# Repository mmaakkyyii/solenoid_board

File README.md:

# solenoid_board
[m5-solenoid_main](https://github.com/mmaakkyyii/m5-solenoid_main)とあわせてソレノイドを駆動するパワーサイドの基板

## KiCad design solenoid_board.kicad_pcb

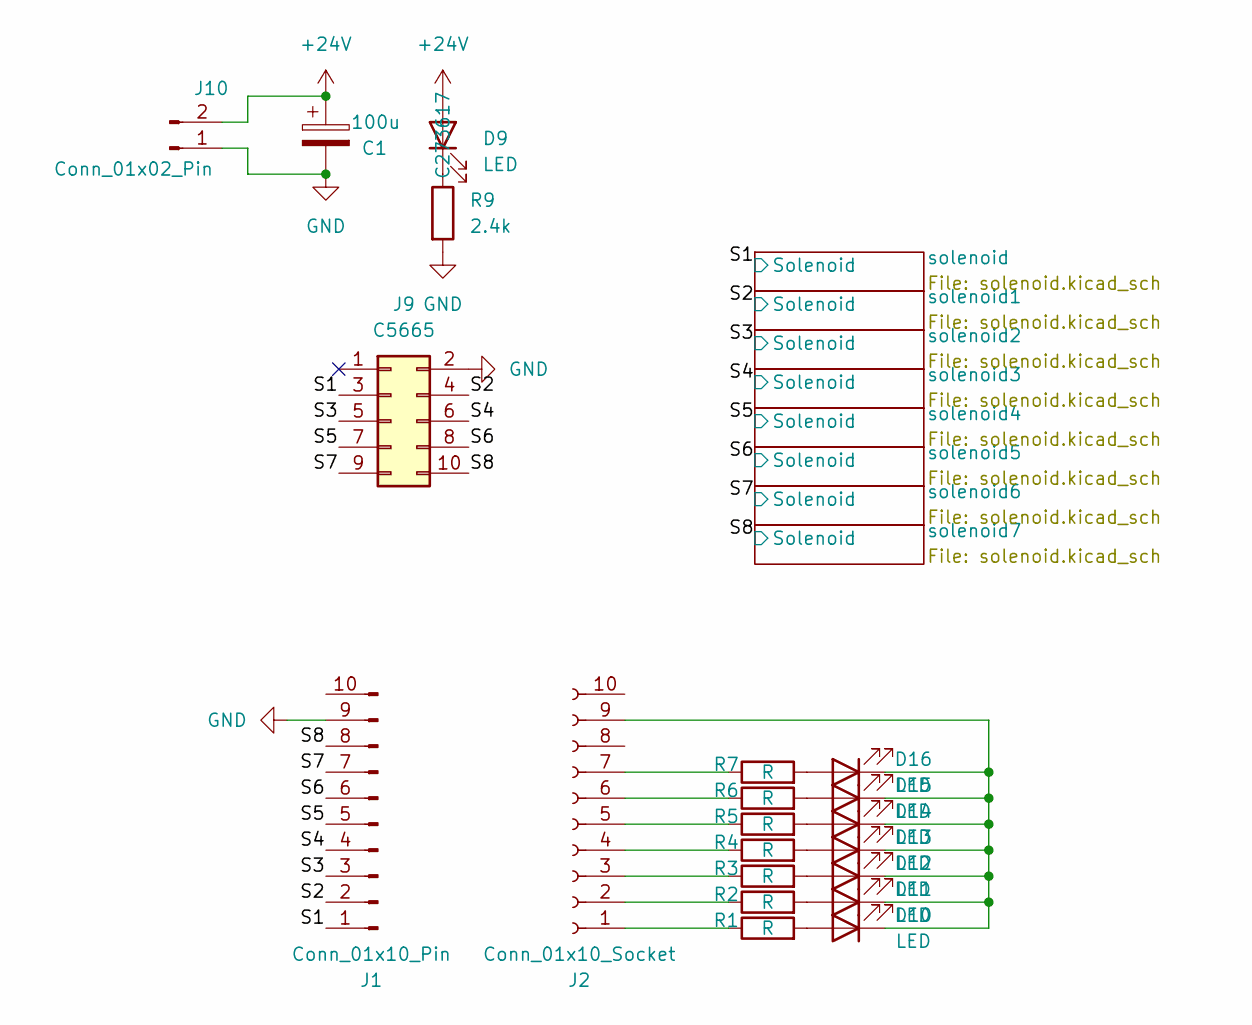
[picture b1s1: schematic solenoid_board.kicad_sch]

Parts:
C1: 100u; CP_Elec_8x10
D9, D10, D11, D12, D13, D14, D15, D16: LED; LED_0603_1608Metric; JLCPCB Parts# C273617
J1: Conn_01x10_Pin; PinSocket_1x10_P2.54mm_Vertical
J2: Conn_01x10_Socket; PinHeader_1x10_P2.54mm_Horizontal
J9: C5665; IDC-Header_2x05_P2.54mm_Vertical
J10: Conn_01x02_Pin; JST_XH_B2B-XH-A_1x02_P2.50mm_Vertical
R1, R2, R3, R4, R5, R6, R7: R; R_0603_1608Metric
R9: 2.4k; R_0603_1608Metric

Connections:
+24V: C1.1, D9.2 (A), J10.2; also elsewhere on the board
/S1: J1.1, J9.3; also elsewhere on the board
/S2: J1.2, J9.4; also elsewhere on the board
/S3: J1.3, J9.5; also elsewhere on the board
/S4: J1.4, J9.6; also elsewhere on the board
/S5: J1.5, J9.7; also elsewhere on the board
/S6: J1.6, J9.8; also elsewhere on the board
/S7: J1.7, J9.9; also elsewhere on the board
/S8: J1.8, J9.10; also elsewhere on the board
GND: C1.2, J1.9, J9.2, J10.1, R9.2; also elsewhere on the board
unnamed: D9.1 (K), R9.1
unnamed: D10.2 (A), R1.2
unnamed: D10.1 (K), D11.1 (K), D12.1 (K), D13.1 (K), D14.1 (K), D15.1 (K), D16.1 (K), J2.9
unnamed: D11.2 (A), R2.2
unnamed: D12.2 (A), R3.2
unnamed: D13.2 (A), R4.2
unnamed: D14.2 (A), R5.2
unnamed: D15.2 (A), R6.2
unnamed: D16.2 (A), R7.2
unnamed: J2.1, R1.1
unnamed: J2.2, R2.1
unnamed: J2.3, R3.1
unnamed: J2.4, R4.1
unnamed: J2.5, R5.1
unnamed: J2.6, R6.1
unnamed: J2.7, R7.1

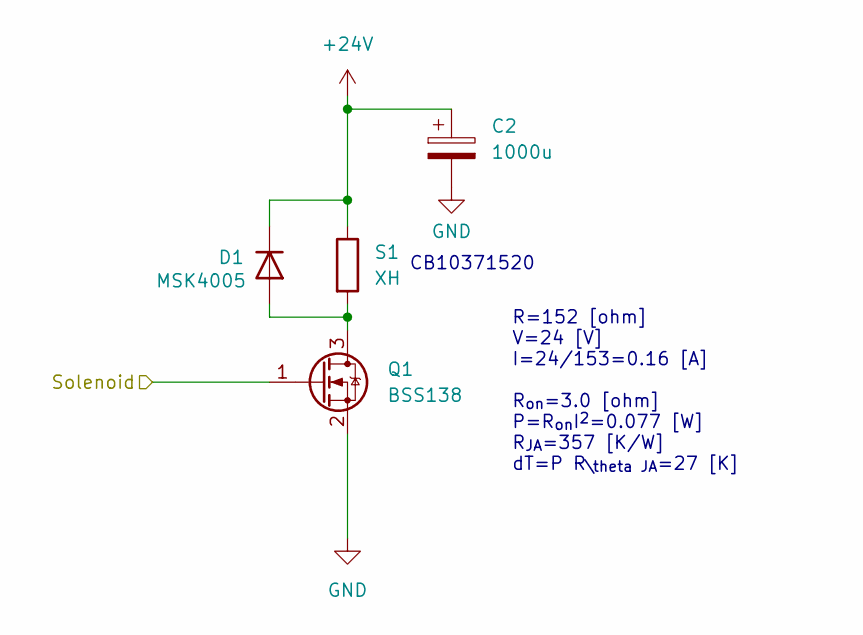
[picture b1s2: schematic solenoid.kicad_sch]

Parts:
C2: 1000u; CP_Radial_D10.0mm_P5.00mm
D1: MSK4005; D_SOD-523
Q1: BSS138; SOT-23; JLCPCB Parts# C427380
S1: XH; JST_XH_B2B-XH-A_1x02_P2.50mm_Vertical

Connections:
+24V: C2.1, D1.1 (K), S1.1; also elsewhere on the board
/S1: Q1.1 (G); also elsewhere on the board
GND: C2.2, Q1.2 (S); also elsewhere on the board
unnamed: D1.2 (A), Q1.3 (D), S1.2

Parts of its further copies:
C3, C4, C5, C6, C7, C8, C9: 1000u; CP_Radial_D10.0mm_P5.00mm
D2, D3, D4, D5, D6, D7, D8: MSK4005; D_SOD-523
Q2, Q3, Q4, Q5, Q6, Q7, Q8: BSS138; SOT-23; JLCPCB Parts# C427380
S2, S3, S4, S5, S6, S7, S8: XH; JST_XH_B2B-XH-A_1x02_P2.50mm_Vertical

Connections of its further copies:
+24V: C3.1, C4.1, C5.1, C6.1, C7.1, C8.1, C9.1, D2.1 (K), D3.1 (K), D4.1 (K), D5.1 (K), D6.1 (K), D7.1 (K), D8.1 (K), S2.1, S3.1, S4.1, S5.1, S6.1, S7.1, S8.1; also elsewhere on the board
/S2: Q2.1 (G); also elsewhere on the board
/S3: Q3.1 (G); also elsewhere on the board
/S4: Q4.1 (G); also elsewhere on the board
/S5: Q5.1 (G); also elsewhere on the board
/S6: Q6.1 (G); also elsewhere on the board
/S7: Q7.1 (G); also elsewhere on the board
/S8: Q8.1 (G); also elsewhere on the board
GND: C3.2, C4.2, C5.2, C6.2, C7.2, C8.2, C9.2, Q2.2 (S), Q3.2 (S), Q4.2 (S), Q5.2 (S), Q6.2 (S), Q7.2 (S), Q8.2 (S); also elsewhere on the board
unnamed: D2.2 (A), Q2.3 (D), S2.2
unnamed: D3.2 (A), Q3.3 (D), S3.2
unnamed: D4.2 (A), Q4.3 (D), S4.2
unnamed: D5.2 (A), Q5.3 (D), S5.2
unnamed: D6.2 (A), Q6.3 (D), S6.2
unnamed: D7.2 (A), Q7.3 (D), S7.2
unnamed: D8.2 (A), Q8.3 (D), S8.2

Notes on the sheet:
CB10371520
R=152 [ohm] V=24 [V] I=24/153=0.16 [A] R_{on}=3.0 [ohm] P=R_{on}I^{2}=0.077 [W] R_{JA}=357 [K/W] dT=P R_{\theta JA}=27 [K]

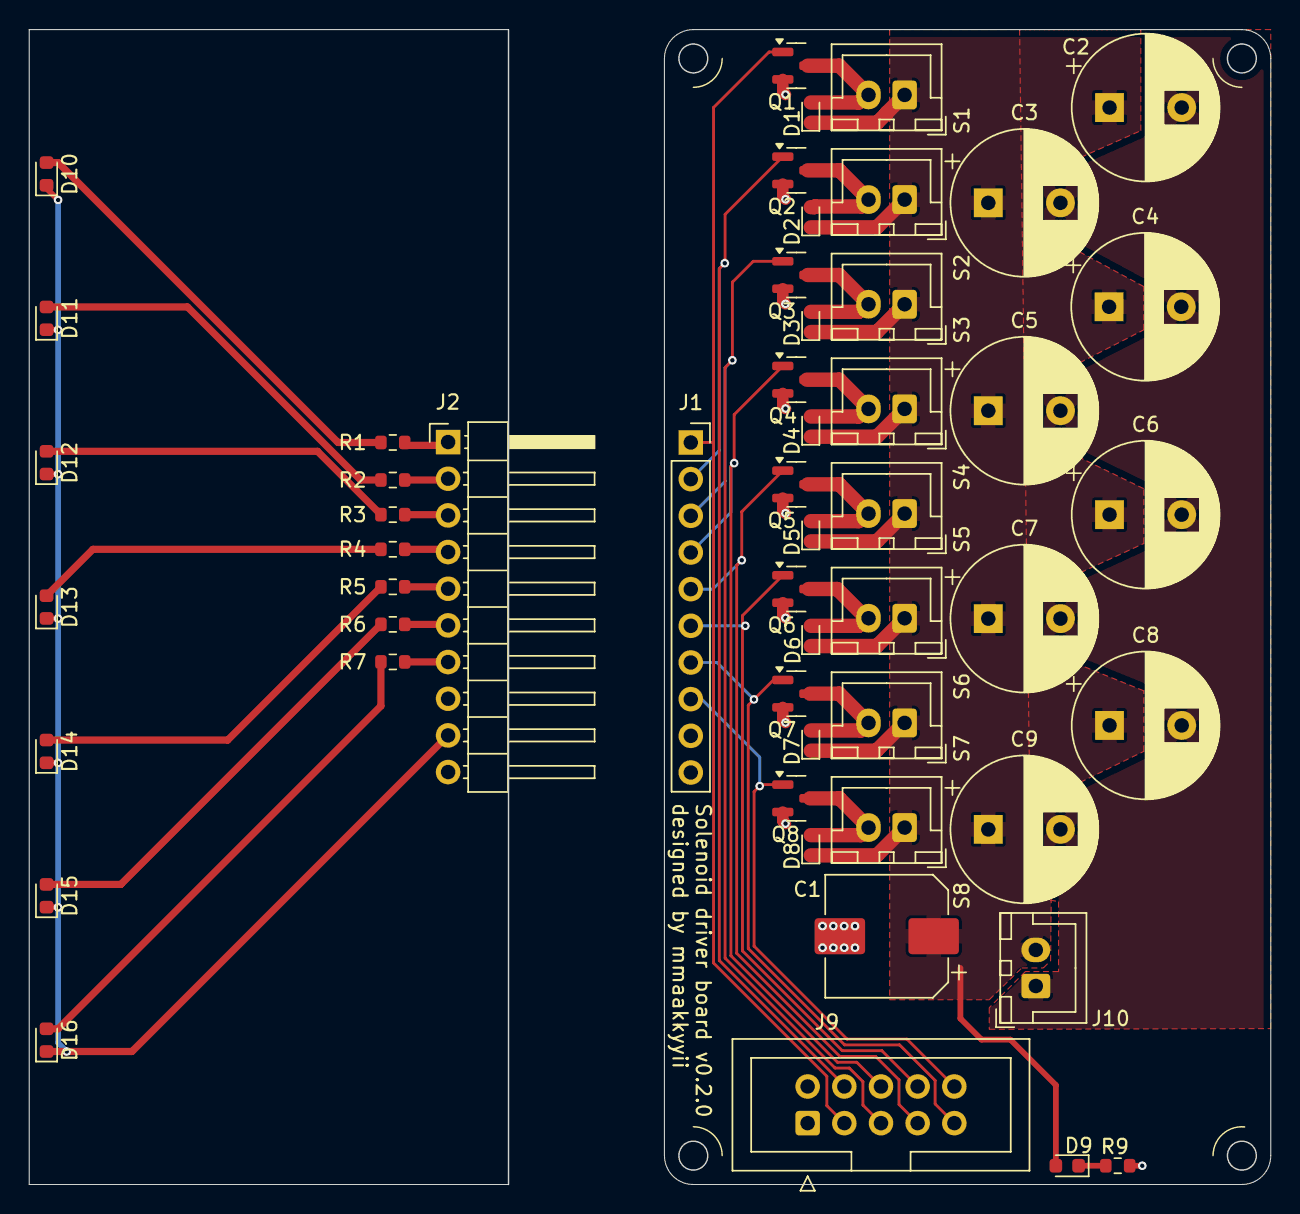
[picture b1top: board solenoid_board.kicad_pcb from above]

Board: 2 copper layers, 86.0 x 80.0 mm, 53 parts (0 on the bottom side), 34 nets.
